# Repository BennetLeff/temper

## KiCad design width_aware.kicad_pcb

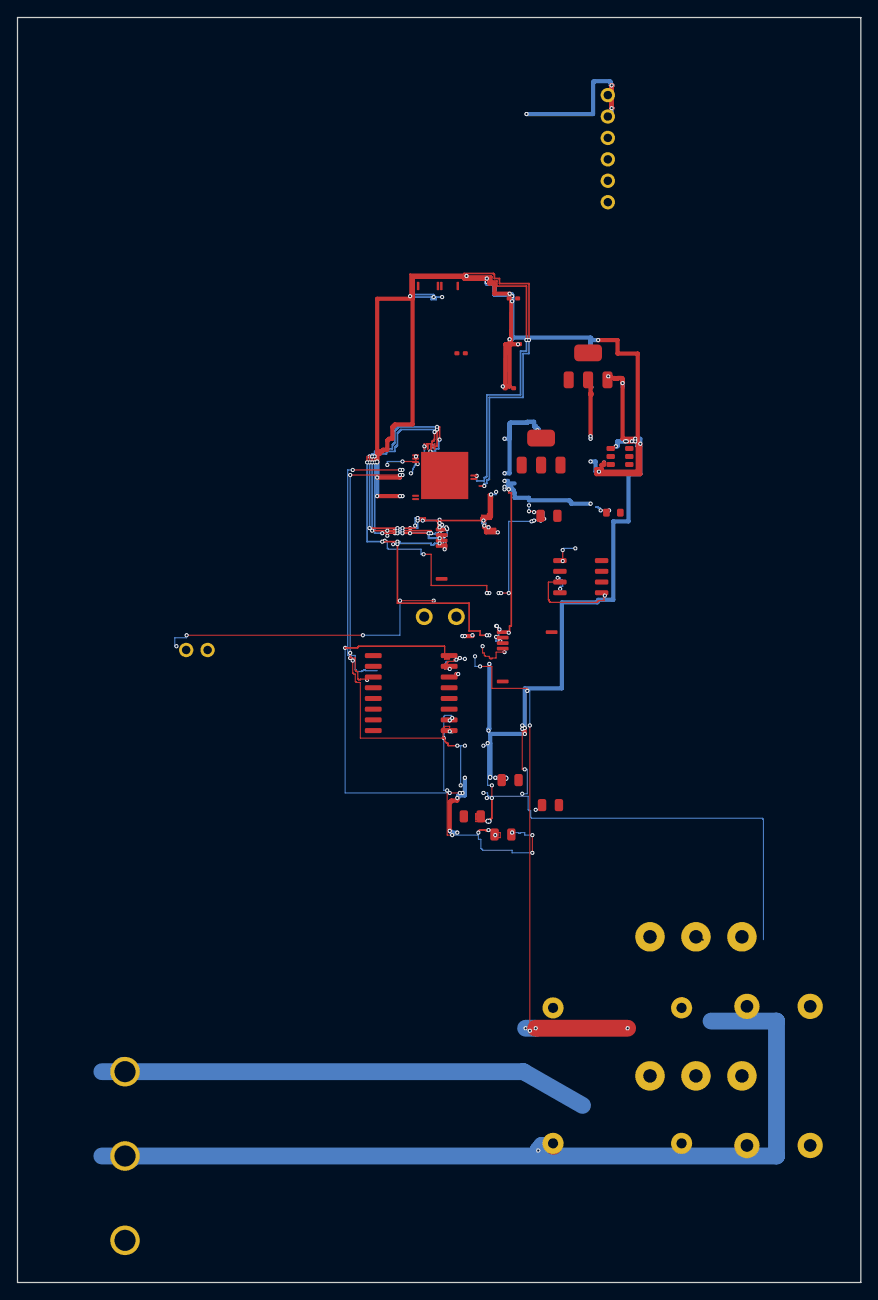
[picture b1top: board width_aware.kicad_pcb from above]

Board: 4 copper layers, 100.0 x 150.0 mm, 33 parts (0 on the bottom side), 23 nets.

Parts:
C_BOOT: 10uF; C_0805_2012Metric
C_BUS1, C_BUS2: 330uF/400V; CP_Radial_D18.0mm_P7.50mm
C_CT_FILT: 100pF; C_0603_1608Metric
C_MCU_1, C_MCU_2, C_MCU_3: 100nF; C_0402_1005Metric
C_MCU_4: 10uF; C_0402_1005Metric
C_VCC: 10uF; C_0805_2012Metric
D1, D2: 1N5408; D_DO-201AD_P15.24mm_Horizontal
J_AC_IN: IEC_C14; IEC_C14_Male
J_COIL: Coil; PhoenixContact_MCV_1,5_2-G-3.81_1x02_P3.81mm_Vertical
J_DEBUG: Debug; PinHeader_1x06_P2.54mm_Vertical
J_NTC: NTC; PinHeader_1x02_P2.54mm_Vertical
J_USB: USB_C; USB_C_Receptacle_HRO_TYPE-C-31-M-12
MAX31865: MAX31865; TSSOP-20_4.4x6.5mm_P0.65mm
MH1, MH2, MH3, MH4: MountingHole_3.2mm_M3
Q1, Q2: IKW40N120H3; TO-247-3_Horizontal_TabDown
R_BURDEN: 33R; R_0805_2012Metric
R_GATE_H: 4.7R; R_0805_2012Metric
R_GATE_L: 4.7R; R_0805_2012Metric
U_BUCK: LMR51430; SOT-23-6
U_CT: MAX31865; TSSOP-20_4.4x6.5mm_P0.65mm
U_GATE: UCC21550; SOIC-16W_7.5x10.3mm_P1.27mm
U_LDO_3V3: AMS1117-3.3; SOT-223-3_TabPin2
U_LDO_5V: AMS1117-5.0; SOT-223-3_TabPin2
U_MCU: ESP32-S3-WROOM-1; QFN-56-1EP_7x7mm_P0.4mm_EP5.6x5.6mm
U_OPAMP_CT: LM358; SOIC-8_3.9x4.9mm_P1.27mm

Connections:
+3V3: C_MCU_1.1, C_MCU_2.1, C_MCU_3.1, C_MCU_4.1, J_DEBUG.2, MAX31865.20, U_CT.20, U_LDO_3V3.2, U_LDO_3V3.4, U_MCU.1
+5V: U_BUCK.2, U_BUCK.4, U_LDO_3V3.3, U_LDO_5V.2, U_LDO_5V.4, U_OPAMP_CT.7, U_OPAMP_CT.8
+15V: C_VCC.1, U_BUCK.3, U_GATE.1, U_GATE.11, U_LDO_5V.3
AC_L: D1.1, J_AC_IN.1
AC_N: D2.2, J_AC_IN.2
CGND: C_VCC.2, U_GATE.5, U_GATE.6, U_GATE.7, U_GATE.8
DC_BUS+: C_BUS1.1, C_BUS2.1, D1.2, Q1.2
GATE_H: Q1.1, R_GATE_H.1, R_GATE_H.2, U_GATE.15
GATE_L: Q2.1, R_GATE_L.1, R_GATE_L.2, U_GATE.10
GND: C_CT_FILT.2, C_MCU_1.2, C_MCU_2.2, C_MCU_3.2, C_MCU_4.2, J_AC_IN.3, J_COIL.2, J_DEBUG.1, J_NTC.2, J_USB.A1, J_USB.A12, MAX31865.10, R_BURDEN.2, U_BUCK.1, U_BUCK.5, U_BUCK.6, U_CT.10, U_LDO_3V3.1, U_LDO_5V.1, U_MCU.2, U_MCU.57, U_OPAMP_CT.4
I_SENSE: C_CT_FILT.1, R_BURDEN.1, U_MCU.15, U_OPAMP_CT.1, U_OPAMP_CT.2, U_OPAMP_CT.3, U_OPAMP_CT.5, U_OPAMP_CT.6
PGND: C_BUS1.2, C_BUS2.2, Q2.3, U_GATE.12, U_GATE.13
PWM_H: U_GATE.2, U_MCU.13
PWM_L: U_GATE.3, U_MCU.14
SPI_CLK: MAX31865.1, U_CT.1, U_MCU.20
SPI_CS_TEMP: U_CT.4, U_MCU.23
SPI_MISO: MAX31865.3, U_CT.3, U_MCU.22
SPI_MOSI: MAX31865.2, U_CT.2, U_MCU.21
SW_NODE: C_BOOT.2, J_COIL.1, Q1.3, Q2.2, U_GATE.9, U_GATE.16
TEMP_SENSE: J_NTC.1, MAX31865.4
USB_D+: J_USB.A6, U_MCU.40
USB_D-: J_USB.B6, U_MCU.41
VCC_BOOT: C_BOOT.1, U_GATE.14

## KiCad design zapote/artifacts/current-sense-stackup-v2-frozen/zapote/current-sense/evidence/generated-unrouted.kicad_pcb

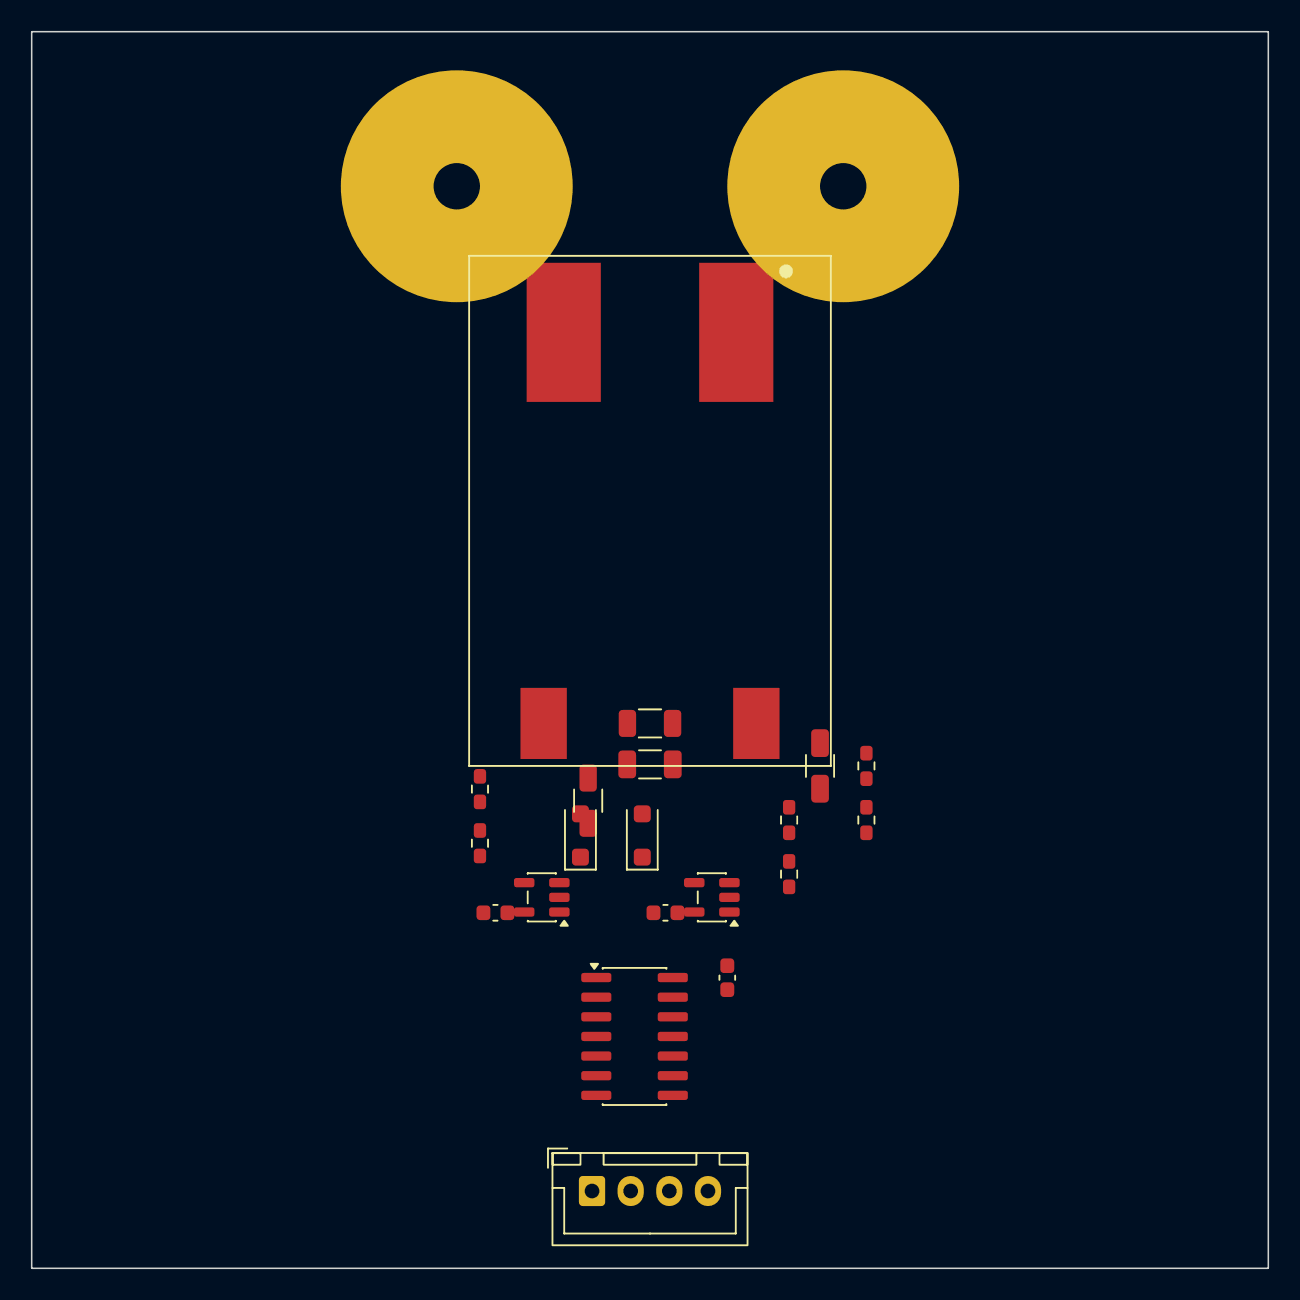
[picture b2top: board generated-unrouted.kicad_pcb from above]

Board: 6 copper layers, 80.0 x 80.0 mm, 21 parts (0 on the bottom side), 12 nets, no tracks yet.

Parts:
C1, C2: 100nF +/- 5%; C_1206_3216Metric
C3, C4, C5: 100nF +/- 10%; C_0603_1608Metric
D1, D2: BAT54H,115; D_SOD-123F
J1: NON_PURCHASED_BARE_LANDS; LitzPad_15A
J2: B4B-XH-A(LF)(SN); JST_XH_B4B-XH-A_1x04_P2.50mm_Vertical
R1: 1.50ohm +/- 1%; R_1206_3216Metric
R2, R3, R6, R7: 10kohm +/- 0.1%; R_0603_1608Metric
R4: 1kohm +/- 1%; R_1206_3216Metric
R5, R8: 3.74kohm +/- 0.1%; R_0603_1608Metric
T1: CST3015-100ED; CST3015_Datasheet2025
U1, U2: TLV3201AIDBVR; SOT-23-5
U3: SN74HC4075DR; SOIC-14_3.9x8.7mm_P1.27mm

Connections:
+3V3: C3.1, C4.1, C5.1, D1.1, J2.1, R2.1, R5.1, R7.1, U1.5, U2.5, U3.14
CT_SENSE: C1.1, R1.1, R4.1, T1.3
OCP_FAULT: J2.3, U3.9
OCP_NEG: U2.1, U3.2
OCP_POS: U1.1, U3.1
PRIMARY_IN: J1.1, T1.1
PRIMARY_OUT: J1.2, T1.2
REF_HI: R5.2, R6.1, U1.4
REF_LO: R7.2, R8.1, U2.3
SENSE_MON: D1.2, D2.1, J2.4, R4.2, U1.3, U2.4
VBIAS: C1.2, C2.1, R1.2, R2.2, R3.1, T1.4
gnd: C2.2, C3.2, C4.2, C5.2, D2.2, J2.2, R3.2, R6.2, R8.2, U1.2, U2.2, U3.3, U3.4, U3.5, U3.7, U3.8, U3.11, U3.12, U3.13

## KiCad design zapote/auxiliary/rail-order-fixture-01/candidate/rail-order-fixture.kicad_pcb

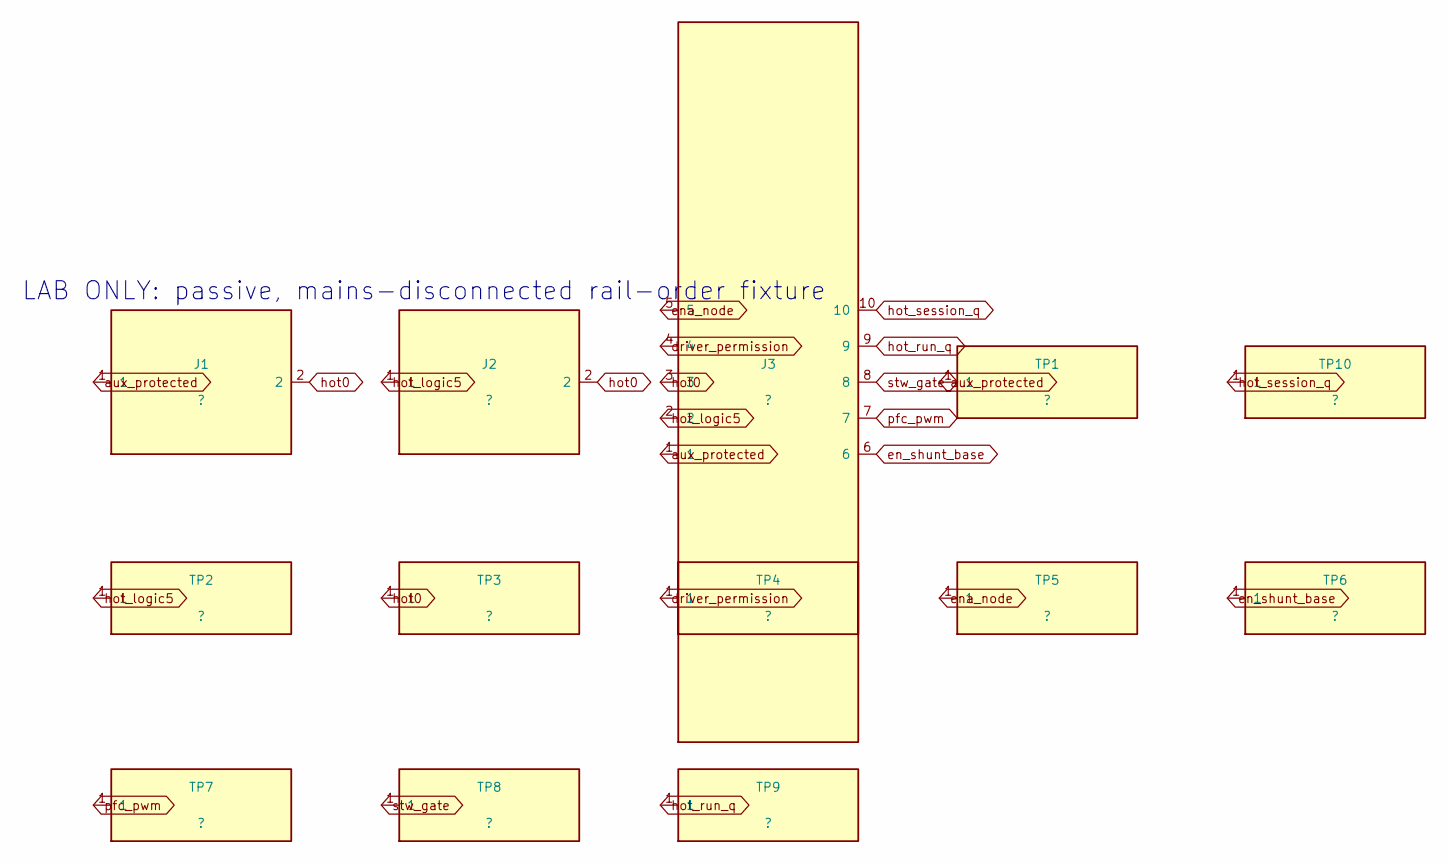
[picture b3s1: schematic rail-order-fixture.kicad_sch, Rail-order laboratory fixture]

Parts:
J1, J2: ?; PinHeader_1x02_P2.54mm_Vertical
J3: ?; PinHeader_1x10_P2.54mm_Vertical
TP1, TP2, TP3, TP4, TP5, TP6, TP7, TP8, TP9, TP10: ?; TestPoint_Pad_D1.0mm

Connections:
aux_protected: J1.1, J3.1, TP1.1
driver_permission: J3.4, TP4.1
en_shunt_base: J3.6, TP6.1
ena_node: J3.5, TP5.1
hot0: J1.2, J2.2, J3.3, TP3.1
hot_logic5: J2.1, J3.2, TP2.1
hot_run_q: J3.9, TP9.1
hot_session_q: J3.10, TP10.1
pfc_pwm: J3.7, TP7.1
stw_gate: J3.8, TP8.1

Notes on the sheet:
LAB ONLY: passive, mains-disconnected rail-order fixture

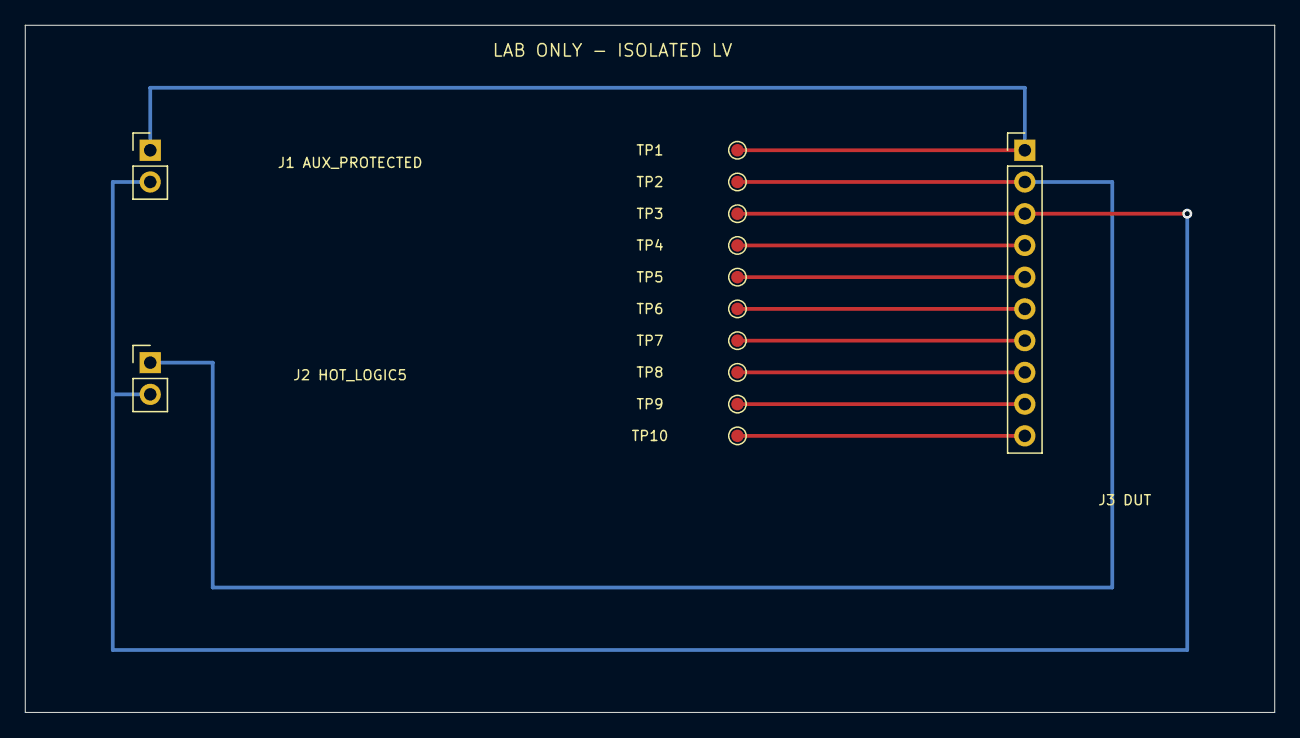
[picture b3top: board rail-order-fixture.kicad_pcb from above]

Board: 2 copper layers, 100.0 x 55.0 mm, 13 parts (0 on the bottom side), 10 nets.
